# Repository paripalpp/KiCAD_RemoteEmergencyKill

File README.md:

# 遠隔緊急緊急停止スイッチ

 遠隔緊急停止スイッチ用基板。子機と親機で共通の基盤を使用。

## KiCADファイル

 KiCADファイルを開くときは[KiCAD_libralies](https://github.com/paripalpp/KiCAD_libralies)を追加して下さい。

## 使用部品

- interplan im920s
  - 920MHz帯の無線ユニットで接点入出力モード(注:ファームウェア1.16以降)をつかってスタンドアロンで動作させる。
  - [製品ページ](https://www.interplan.co.jp/solution/wireless/im920s/)
- JST XAコネクタ
  - 2.54mmピッチの圧着コネクタでサイド型を信号出力、電源に使用
  - [製品ページ](https://www.jst-mfg.com/product/detail.php?series=272)
- IS-1245T-G
  - Switronicの基板用スライドスイッチ、電源スイッチに使用
  - [datasheet](https://akizukidenshi.com/download/ds/switronic/IS-1245T-G.PDF)
- LP401730
  - 1sell LiPoバッテリー 150mA
  - [datasheet](https://www.eemb.com/public/Download/Rechargeable-Lithium-Battery/Li-Polymer-Battery/Standard-Version/LP401730.pdf)
- MCP73831-2ATI/OT
  - 単セルLiPoバッテリー充電コントローラicで子機のLiPoバッテリーを充電する
  - [datasheet](https://akizukidenshi.com/download/ds/microchip/mcp73831_73832.pdf)
- RBS1MM40ATR
  - 超低Vfショットキーバリアダイオード、電源供給を5V(外部)とLiPoバッテリー(内蔵)で切り替える
  - [製品ページ](https://www.rohm.co.jp/products/diodes/schottky-barrier-diodes/ultra-low-vf/rb161mm-20-product)
- ADP151AUJZ-3.3
  - 低雑音、低損失リニアレギュレータ、im920への電源供給用
  - [datasheet](https://akizukidenshi.com/download/ds/analog/ADP151_jp.pdf)

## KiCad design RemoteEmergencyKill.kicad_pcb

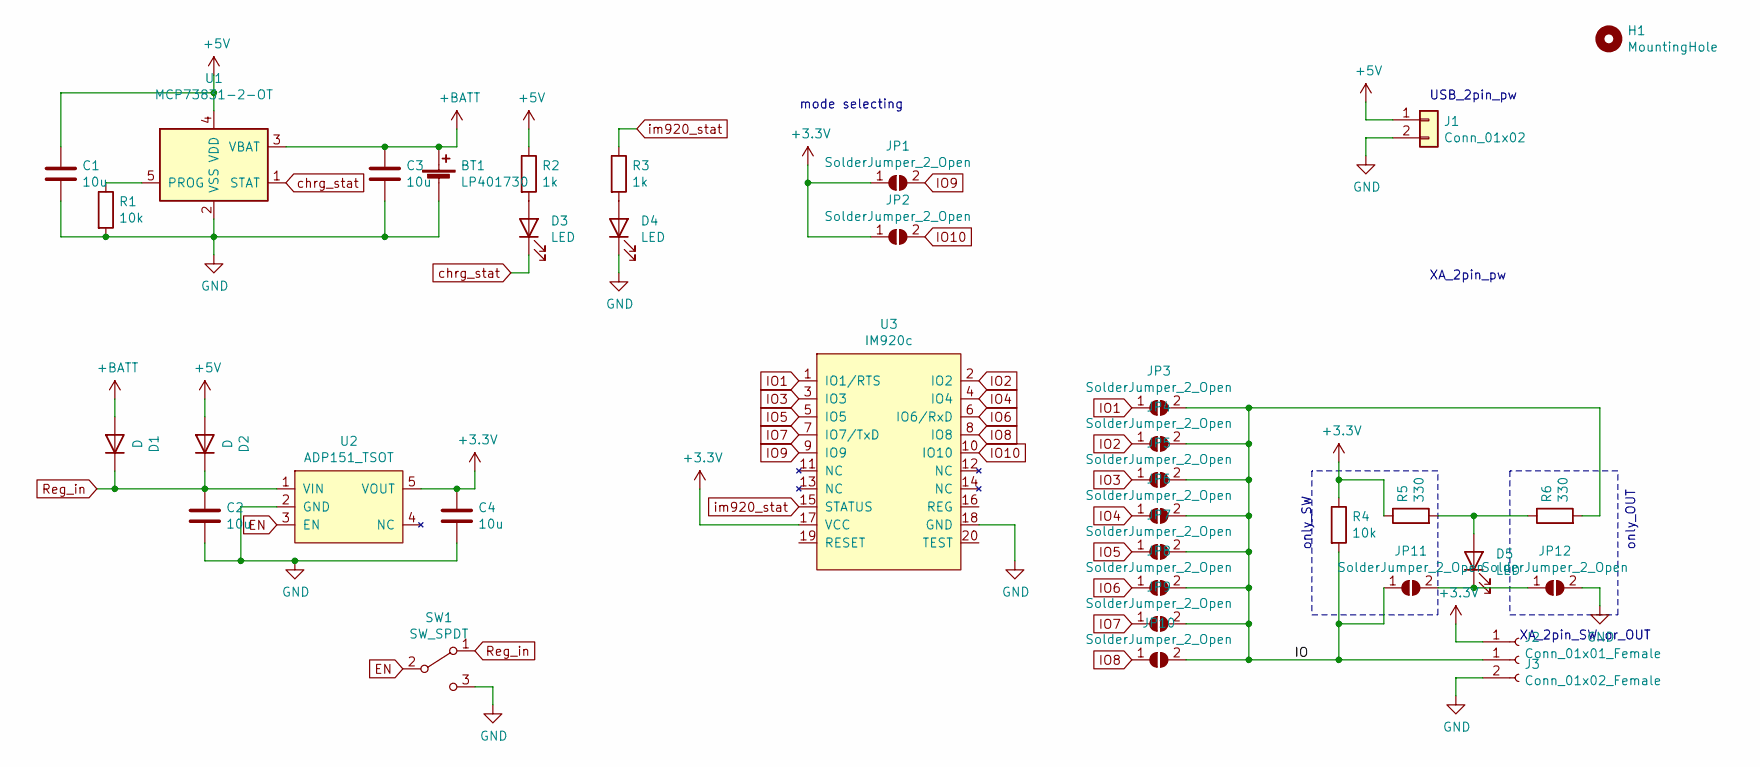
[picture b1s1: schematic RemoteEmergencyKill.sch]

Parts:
BT1: LP401730
C1, C2, C3, C4: 10u; C_0805_2012Metric
D1, D2: D; D_SOD-123F
D3, D4, D5: LED; LED_0603_1608Metric
H1: MountingHole; MountingHole_2.2mm_M2_Pad_Via
J1: Conn_01x02; USB micro B 2pin
J2: Conn_01x01_Female; PinSocket_1x01_P2.54mm_Horizontal
J3: Conn_01x02_Female; JST_XA_S02B-XASK-1_1x02_P2.50mm_Horizontal
JP1, JP2, JP3, JP4, JP5, JP6, JP7, JP8, JP9, JP10, JP11, JP12: SolderJumper_2_Open; SolderJumper-2_P1.3mm_Open_TrianglePad1.0x1.5mm
R1, R4: 10k; R_0603_1608Metric
R2, R3: 1k; R_0603_1608Metric
R5, R6: 330; R_0603_1608Metric
SW1: SW_SPDT; IS-1245T-G
U1: MCP73831-2-OT; SOT-23-5
U2: ADP151_TSOT; TSOT-23-5
U3: IM920c

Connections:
+3V3: C4.1, J2.1, JP1.1 (A), JP2.1 (A), R4.1, R5.1, U2.5 (VOUT), U3.17 (VCC)
+5V: C1.1, D2.2 (A), J1.1, R2.1, U1.4 (VDD)
+BATT: BT1.1 (+), C3.1, D1.2 (A), U1.3 (VBAT)
/IO: J3.1, JP3.2 (B), JP4.2 (B), JP5.2 (B), JP6.2 (B), JP7.2 (B), JP8.2 (B), JP9.2 (B), JP10.2 (B), JP11.1 (A), R4.2, R6.2
EN: SW1.2 (B), U2.3 (EN)
GND: BT1.2 (-), C1.2, C2.2, C3.2, C4.2, D4.1 (K), J1.2, J3.2, JP12.2 (B), R1.2, SW1.3 (C), U1.2 (VSS), U2.2 (GND), U3.18 (GND)
IO1: JP3.1 (A), U3.1 (IO1/RTS)
IO2: JP4.1 (A), U3.2 (IO2)
IO3: JP5.1 (A), U3.3 (IO3)
IO4: JP6.1 (A), U3.4 (IO4)
IO5: JP7.1 (A), U3.5 (IO5)
IO6: JP8.1 (A), U3.6 (IO6/RxD)
IO7: JP9.1 (A), U3.7 (IO7/TxD)
IO8: JP10.1 (A), U3.8 (IO8)
IO9: JP1.2 (B), U3.9 (IO9)
IO10: JP2.2 (B), U3.10 (IO10)
unnamed: D3.2 (A), R2.2
unnamed: D4.2 (A), R3.2
unnamed: D5.1 (K), JP11.2 (B), JP12.1 (A)
unnamed: D5.2 (A), R5.2, R6.1
unnamed: R1.1, U1.5 (PROG)
Reg_in: C2.1, D1.1 (K), D2.1 (K), SW1.1 (A), U2.1 (VIN)
chrg_stat: D3.1 (K), U1.1 (STAT)
im920_stat: R3.1, U3.15 (STATUS)

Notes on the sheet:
mode selecting
USB_2pin_pw
XA_2pin_pw
only_SW
XA_2pin_SW_or_OUT
only_OUT

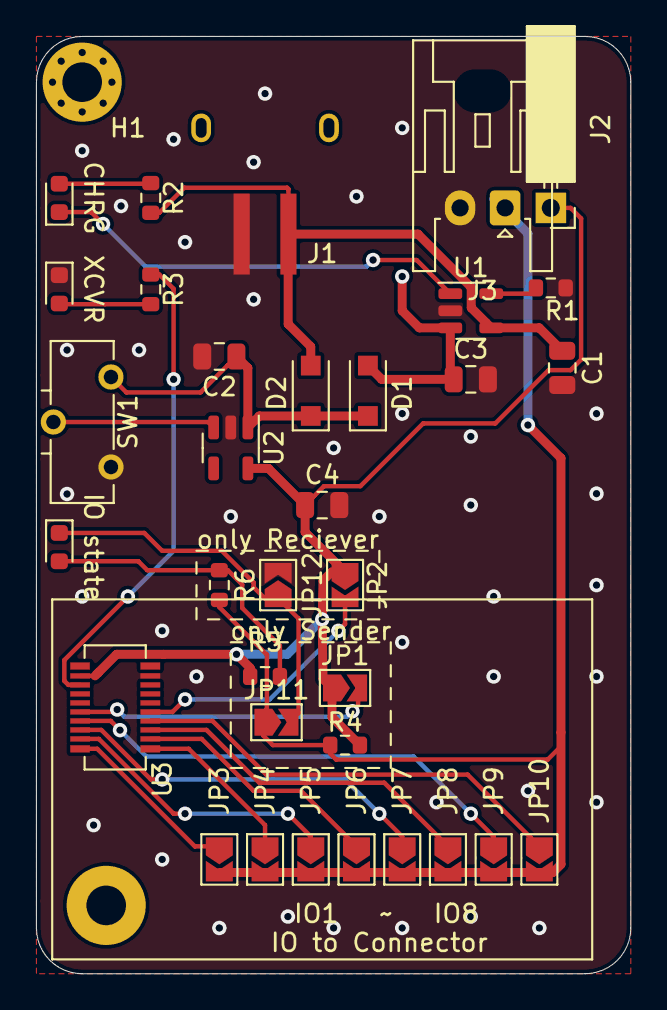
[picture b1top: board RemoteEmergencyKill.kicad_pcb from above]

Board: 2 copper layers, 33.0 x 52.1 mm, 36 parts (1 on the bottom side), 24 nets.

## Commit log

2021-07-02 README added
2021-07-03 starting to make schmatic
2021-07-04 schematic update
2021-07-05 changed regulator
2021-07-07 pcb file added
2021-07-07 README updated
2021-07-08 complete!!!
2021-07-08 proted gbr files
2021-08-26 cache?
2021-08-26 chenge schematic
2021-08-26 completed
2021-08-27 gaebar
